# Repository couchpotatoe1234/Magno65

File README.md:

## Magno65
After weeks of hard work, here it is. The first prototype of the Magno65.

It will use N52 Neodymium magnets that are 5mmx2mm in the PCB and on the bottom of the case, allowing the plate and the PCB to levitate. 

The case itself is two parts, so it is 3D-printable. I currently have some untested firmware that will be tested when I make this project. Heres the aproximate BOM currently.
| Name                     | Purpose                                            | Quantity | Total Cost (USD) | Link                                                                                                                                                                                                                                                                                                                                                                                                                                                                                                                                                                                                                                                                                                                                                                                                                                                                                                                                                                                                                                                                                                                                                                                                                                                                                                                                                                                | Distributor       |
|--------------------------|----------------------------------------------------|----------|------------------|-------------------------------------------------------------------------------------------------------------------------------------------------------------------------------------------------------------------------------------------------------------------------------------------------------------------------------------------------------------------------------------------------------------------------------------------------------------------------------------------------------------------------------------------------------------------------------------------------------------------------------------------------------------------------------------------------------------------------------------------------------------------------------------------------------------------------------------------------------------------------------------------------------------------------------------------------------------------------------------------------------------------------------------------------------------------------------------------------------------------------------------------------------------------------------------------------------------------------------------------------------------------------------------------------------------------------------------------------------------------------------------|-------------------|
| PCB                      | THE PCB, THE MAIN PART                             | 1        | 22.60            | https://jlcpcb.com                                                                                                                                                                                                                                                                                                                                                                                                                                                                                                                                                                                                                                                                                                                                                                                                                                                                                                                                                                                                                                                                                                                                                                                                                                                                                                                                                                  | JLCPCB            |
| N52 Neodymium magnets    | to levitate the PCB (smallest pack I could find)   | 1        | 12.04            | https://www.greenstuffworld.com/en/neodymium-magnets-n52/503-neodymium-magnets-5x2mm-50-units-n52.html                                                                                                                                                                                                                                                                                                                                                                                                                                                                                                                                                                                                                                                                                                                                                                                                                                                                                                                                                                                                                                                                                                                                                                                                                                                                              | Green Stuff World |
| Keyboard Stabilizers     | to stabilize the keycaps                           | 1        | 7.55             | https://www.temu.com/gold-plated-plate-mounted-stabilizer-for-custom-mechanical-keyboard-2u-6-25u-g-601100064817086.html?_oak_mp_inf=EL7%2F2Z6o1ogBGiBhMzZlYTk0MDE5MDM0NmMyODM0NzBlNDU1ZjBkMDlmNCC4grKg2DM%3D&top_gallery_url=https%3A%2F%2Fimg.kwcdn.com%2Fproduct%2Fopen%2Fd60568b099454d8eb8d5ba905d9cdf42-goods.jpeg&spec_gallery_id=393266&refer_page_sn=10009&freesia_scene=2&_oak_freesia_scene=2&_oak_rec_ext_1=NzU1&_oak_gallery_order=289069023%2C1381943868%2C460904097%2C430772795%2C1266147886&search_key=keyboard%20stabilizers&refer_page_el_sn=200049&ab_scene=0&enable_vqr=0&_x_sessn_id=wn14p9w9rk&refer_page_name=search_result&refer_page_id=10009_1776036808997_7foyaswubl                                                                                                                                                                                                                                                                                                                                                                                                                                                                                                                                                                                                                                                                                     | Temu              |
| usb micro to usb-c cable | to connect the keyboard to the computer            | 1        | 2.71             | https://www.temu.com/5a-type-c-to-micro-usb-fast-charging-cable-data-tansmission-stable-current-micro-usb-to-type-c-fast-charging-data-cable-for-samsung-xiaomi-huawei-oppo-vivo-high---data-transfer-stable--flexible-charging-cord-g-601104579509990.html?_oak_name_id=9149517372169643071&_oak_mp_inf=EOb9vIe51ogBGiAyZTAxZWY4OTRiNDI0Njk2ODY5YTBmMDNjYmFjMTRiZCDHubrF2TM%3D&top_gallery_url=https%3A%2F%2Fimg.kwcdn.com%2Fproduct%2Ffancy%2Fda51984b-53ff-40e5-8730-5d485981ee59.jpg&spec_gallery_id=261625&refer_page_sn=10009&freesia_scene=2&_oak_freesia_scene=2&_oak_rec_ext_1=Mjcx&_oak_gallery_order=2142591388%2C62159532%2C433164792%2C413324470%2C631688684&search_key=USB-micro%20%20to%20USB%20C%20data%20cable&refer_page_el_sn=200049&ab_scene=0&enable_vqr=1&_x_sessn_id=jb5si0zpbp&refer_page_name=search_result&refer_page_id=10009_1776383073866_u557bmamcj                                                                                                                                                                                                                                                                                                                                                                                                                                                                                                   | Temu              |
| Keycaps                  | to cap the keys                                    | 1        | 6.93             | https://www.temu.com/chic-keycaps-with-contour-lines-featuring--cherry-profile-consisting-of-97-keys--double-shot--for---keycaps-have-see-through--and-lines-g-601100242084406.html?top_gallery_url=https%3A%2F%2Fimg.kwcdn.com%2Fproduct%2Ffancy%2Fb366fc6c-a63f-47c5-8457-d1d9722e4f54.jpg&spec_gallery_id=543959&sku_id=17595324095682&share_token=9SXbwjGQVvLN6AO53nGwdSsUjAHTKImzPHW_I8MpLbxXkFdfj7VuzHuMNDMW4RcFgEqpbDA2upZXWQSFJtAKj5j0HpVFpJCpJvDXVilPGBAXoFHNXLZ6pTCILVGUqEs-&_x_vst_scene=adg&_x_ads_sub_channel=shopping&_x_ns_prz_type=-1&_x_ns_sku_id=17595324095682&_x_ns_gid=601100242084406&_x_ads_channel=google&_x_gmc_account=647900107&_x_login_type=Google&_x_ns_gg_lnk_type=adr&_x_ads_account=1919904652&_x_ads_set=23247691873&_x_ads_id=187675937039&_x_ads_creative_id=783286179500&_x_ns_source=g&_x_ns_gclid=CjwKCAjw4ufOBhBkEiwAfuC7-UZCRVvgkzCTDwP36QHYZFekTYgLvvixg20i3j8YRcbgYLOlBl8YVxoCQrMQAvD_BwE&_x_ns_placement=&_x_ns_match_type=&_x_ns_ad_position=&_x_ns_product_id=17595324095682&_x_ns_target=&_x_ns_devicemodel=&_x_ns_wbraid=CkAKCAjwv-LOBhAqEjAADfTDQ57mPWh-82gaj2x_fIcqDOgOiXeyfZ63v2ajT7DN7h4Hyk_YQIfNX7wuApAaAqFg&_x_ns_gbraid=0AAAAAo4mICFO7USGgQmlUADytEljoZTBi&_x_ns_targetid=pla-2449976477415&refer_page_name=kuiper&refer_page_id=13554_1775933032362_l0cclbjv3z&refer_page_sn=13554&_x_sessn_id=g915edwnry&no_cache_id=v32fd | Temu              |
| Pi Pico                  | the brains of the operation                        | 1        | 3.11             | https://www.temu.com/1pc-sensor-module-pico-development-board--pico---supports--python-low-power-consumption--compatible-with--ide-and-csdk-industrial-electronics-no-battery-no-laser-no-power-supply-material-g-601101152060856.html?_oak_name_id=6196207251010431518&_oak_mp_inf=ELiLkqWs1ogBGiBlMDU1NTAzMzAyNTI0YjMwYTU4M2EwYzljOTMxY2Q2MiDKs7bF2TM%3D&top_gallery_url=https%3A%2F%2Fimg.kwcdn.com%2Fproduct%2Ffancy%2F4f114b41-fe38-4c86-ba03-02ec2a3dbbf5.jpg&spec_gallery_id=487416&refer_page_sn=10009&freesia_scene=2&_oak_freesia_scene=2&_oak_rec_ext_1=MjUy&_oak_gallery_order=299434050%2C1788024366%2C1629561563%2C784285033&search_key=raspberry%20pi%20pico%20rp2040&refer_page_el_sn=200049&ab_scene=0&enable_vqr=1&_x_sessn_id=sfkm1vnct9&refer_page_name=search_result&refer_page_id=10009_1776383007634_b0dhtdh5bt                                                                                                                                                                                                                                                                                                                                                                                                                                                                                                                                              | Temu              |
| Male pin headers         | these are to connect the pi to the board           | 1        | 2.27             | https://www.temu.com/dual-row-2-54mm-pitch-male-pin--40-pin-pcb-connector-strip-for--embedded-systems-g-606045468466813.html?_oak_name_id=5308195194819228546&_oak_mp_inf=EP289qaf5okBGiBmYTI0ZDYwMDQ5NTY0NDc5ODE3OTY4Y2JlYzg3MzViNSDv9fOX2DM%3D&top_gallery_url=https%3A%2F%2Fimg.kwcdn.com%2Fproduct%2Fopen%2F71f1f25fde7d4121ad8cf00ed77ffae3-goods.jpeg&spec_gallery_id=513684&refer_page_sn=10009&freesia_scene=2&_oak_freesia_scene=2&_oak_rec_ext_1=MTQ0&_oak_gallery_order=1559177372%2C921529512%2C483001345%2C1617419758%2C2126600602&search_key=20%20pin%20male%20header&refer_page_el_sn=200049&ab_scene=0&enable_vqr=0&refer_page_name=search_result&refer_page_id=10009_1776019078036_leadu12nfu&_x_sessn_id=sfkm1vnct9                                                                                                                                                                                                                                                                                                                                                                                                                                                                                                                                                                                                                                               | Temu              |
| 1N4148                   | the diodes to make the keyboard work               | 1        | 2.32             | https://www.temu.com/100pcs-1n4148-in4148-do-35-switch-diode-uncharged-other-material-for--g-601100062954719.html?_oak_name_id=417209526502550354&_oak_mp_inf=EN%2Bp6J2o1ogBGiAxNzEzZTYyYzRjYzI0ZmQ1YjZiMWVlNDAyNWZhZDQyNCD44vaX2DM%3D&top_gallery_url=https%3A%2F%2Fimg.kwcdn.com%2Fproduct%2Ffancy%2Fmarket%2Ff59eac153d7334a99a68b11075357811_5hFREXPAsaAaP.jpg&spec_gallery_id=1&refer_page_sn=10009&freesia_scene=2&_oak_freesia_scene=2&_oak_rec_ext_1=MTU0&_oak_gallery_order=1414014030%2C1973228982%2C2050237809%2C1124613986%2C850893309&search_key=1N914&refer_page_el_sn=200049&ab_scene=0&enable_vqr=0&refer_page_name=search_result&refer_page_id=10009_1776019078036_leadu12nfu&_x_sessn_id=sfkm1vnct9                                                                                                                                                                                                                                                                                                                                                                                                                                                                                                                                                                                                                                                               | Temu              |
| Key switches             | these are the whole point of a mechanical keyboard | 1        | 19.99            | https://www.wobkey.com/collections/all/products/keebmonkey-wobkey-rainy75-pre-lubed-hmx-jwk-switches                                                                                                                                                                                                                                                                                                                                                                                                                                                                                                                                                                                                                                                                                                                                                                                                                                                                                                                                                                                                                                                                                                                                                                                                                                                                                | WOBKEY            |

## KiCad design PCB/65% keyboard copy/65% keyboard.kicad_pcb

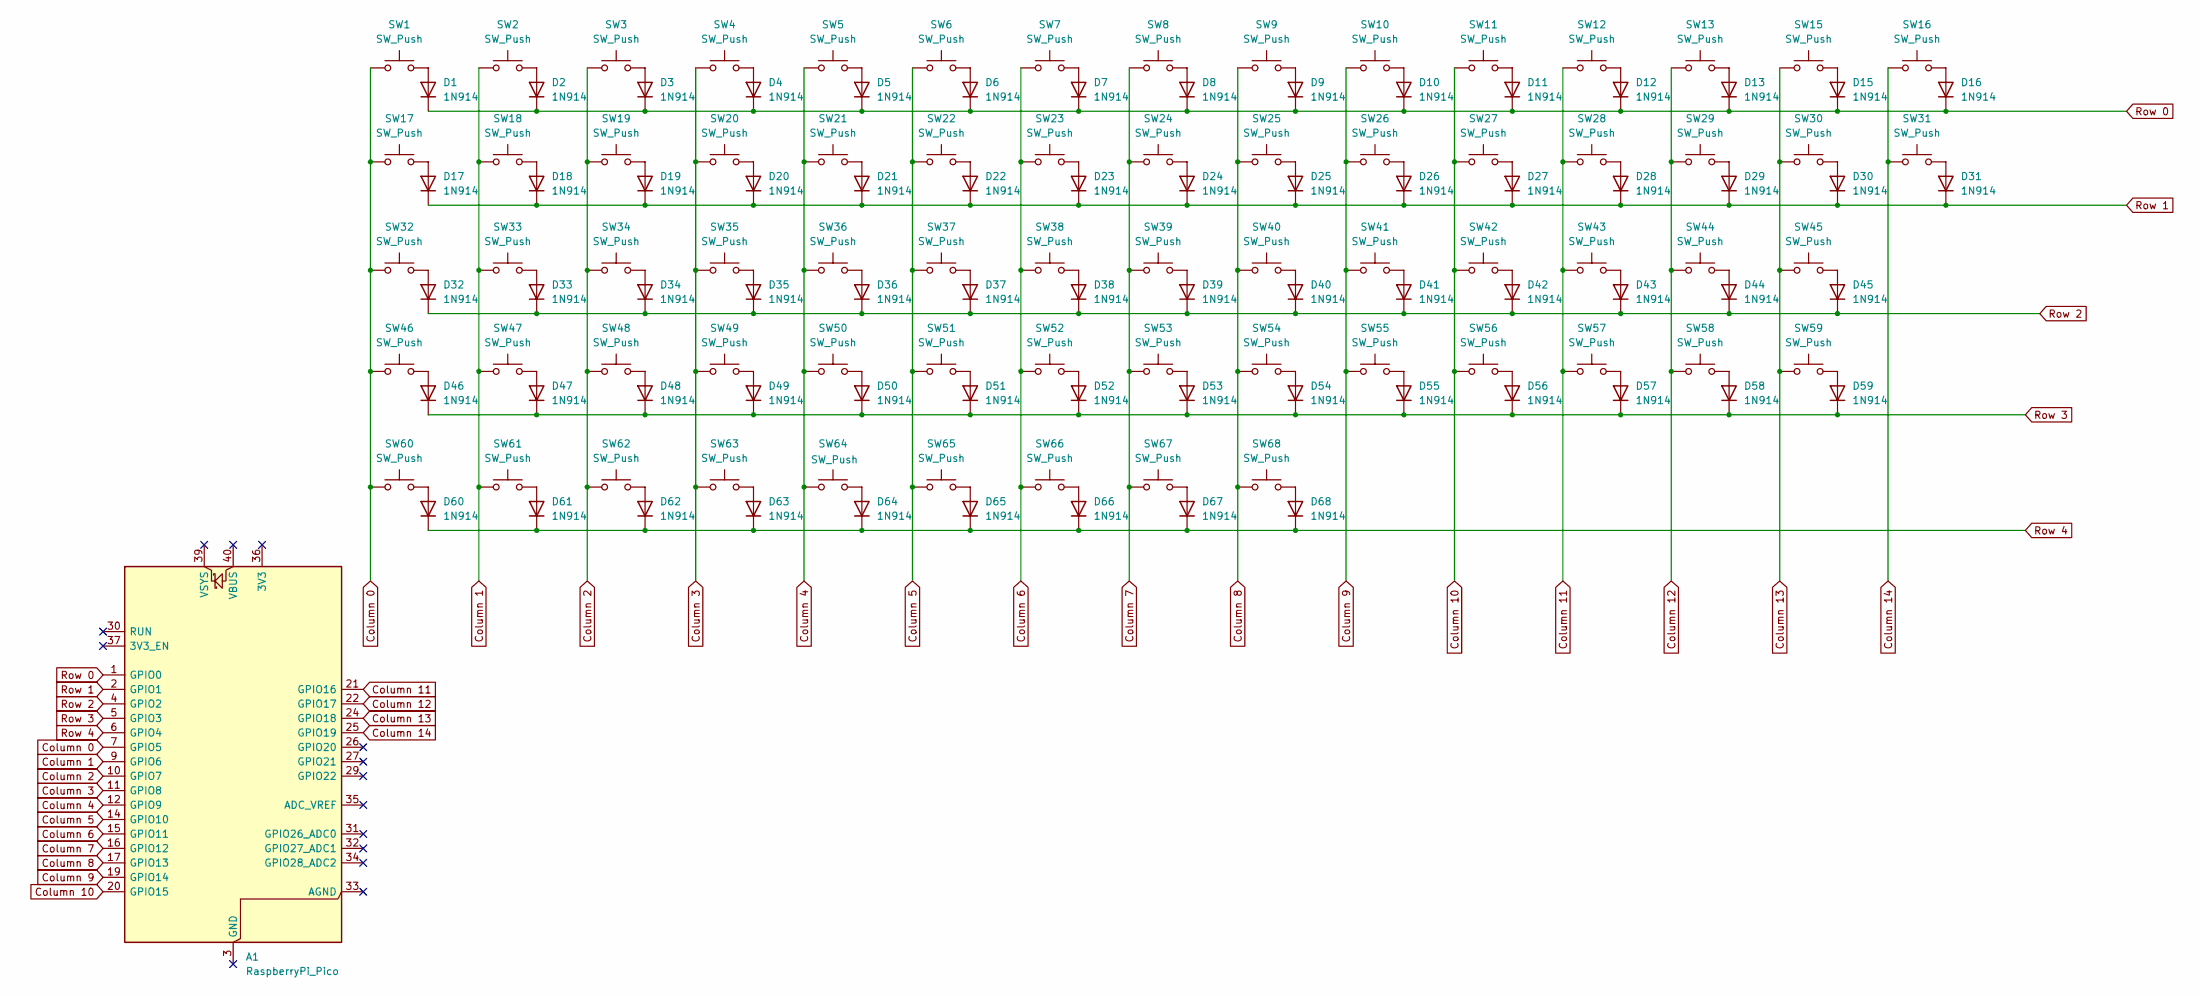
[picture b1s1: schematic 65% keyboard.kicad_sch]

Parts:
A1: RaspberryPi_Pico; RaspberryPi_Pico_Common_Unspecified
D1, D2, D3, D4, D5, D6, D7, D8, D9, D10, D11, D12, D13, D15, D16, D17, D18, D19, D20, D21, D22, D23, D24, D25, D26, D27, D28, D29, D30, D31, D32, D33, D34, D35, D36, D37, D38, D39, D40, D41, D42, D43, D44, D45, D46, D47, D48, D49, D50, D51, D52, D53, D54, D55, D56, D57, D58, D59, D60, D61, D62, D63, D64, D65, D66, D67, D68: 1N914; D_DO-35_SOD27_P7.62mm_Horizontal
SW1, SW2, SW3, SW4, SW5, SW6, SW7, SW8, SW9, SW10, SW11, SW12, SW13, SW16, SW17, SW18, SW19, SW20, SW21, SW22, SW23, SW24, SW25, SW26, SW27, SW28, SW29, SW30, SW31, SW32, SW33, SW34, SW35, SW36, SW37, SW38, SW39, SW40, SW41, SW42, SW43, SW45, SW47, SW48, SW49, SW50, SW51, SW52, SW53, SW54, SW55, SW56, SW57, SW58, SW59, SW60, SW61, SW64, SW65, SW66, SW67, SW68: SW_Push; SW_Cherry_MX_1.00u_PCB
SW15: SW_Push; SW_Cherry_MX_2.00u_Plate
SW44, SW46: SW_Push; SW_Cherry_MX_2.25u_Plate
SW62: SW_Push; SW_Cherry_MX_1.00u_Plate
SW63: SW_Push; SW_Cherry_MX_6.25u_Plate

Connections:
Column 0: A1.7 (GPIO5), SW1.1, SW17.1, SW32.1, SW46.1, SW60.1
Column 1: A1.9 (GPIO6), SW2.1, SW18.1, SW33.1, SW47.1, SW61.1
Column 2: A1.10 (GPIO7), SW3.1, SW19.1, SW34.1, SW48.1, SW62.1
Column 3: A1.11 (GPIO8), SW4.1, SW20.1, SW35.1, SW49.1, SW63.1
Column 4: A1.12 (GPIO9), SW5.1, SW21.1, SW36.1, SW50.1, SW64.1
Column 5: A1.14 (GPIO10), SW6.1, SW22.1, SW37.1, SW51.1, SW65.1
Column 6: A1.15 (GPIO11), SW7.1, SW23.1, SW38.1, SW52.1, SW66.1
Column 7: A1.16 (GPIO12), SW8.1, SW24.1, SW39.1, SW53.1, SW67.1
Column 8: A1.17 (GPIO13), SW9.1, SW25.1, SW40.1, SW54.1, SW68.1
Column 9: A1.19 (GPIO14), SW10.1, SW26.1, SW41.1, SW55.1
Column 10: A1.20 (GPIO15), SW11.1, SW27.1, SW42.1, SW56.1
Column 11: A1.21 (GPIO16), SW12.1, SW28.1, SW43.1, SW57.1
Column 12: A1.22 (GPIO17), SW13.1, SW29.1, SW44.1, SW58.1
Column 13: A1.24 (GPIO18), SW15.1, SW30.1, SW45.1, SW59.1
Column 14: A1.25 (GPIO19), SW16.1, SW31.1
unnamed: D1.2 (A), SW1.2
unnamed: D2.2 (A), SW2.2
unnamed: D3.2 (A), SW3.2
unnamed: D4.2 (A), SW4.2
unnamed: D5.2 (A), SW5.2
unnamed: D6.2 (A), SW6.2
unnamed: D7.2 (A), SW7.2
unnamed: D8.2 (A), SW8.2
unnamed: D9.2 (A), SW9.2
unnamed: D10.2 (A), SW10.2
unnamed: D11.2 (A), SW11.2
unnamed: D12.2 (A), SW12.2
unnamed: D13.2 (A), SW13.2
unnamed: D15.2 (A), SW15.2
unnamed: D16.2 (A), SW16.2
unnamed: D17.2 (A), SW17.2
unnamed: D18.2 (A), SW18.2
unnamed: D19.2 (A), SW19.2
unnamed: D20.2 (A), SW20.2
unnamed: D21.2 (A), SW21.2
unnamed: D22.2 (A), SW22.2
unnamed: D23.2 (A), SW23.2
unnamed: D24.2 (A), SW24.2
unnamed: D25.2 (A), SW25.2
unnamed: D26.2 (A), SW26.2
unnamed: D27.2 (A), SW27.2
unnamed: D28.2 (A), SW28.2
unnamed: D29.2 (A), SW29.2
unnamed: D30.2 (A), SW30.2
unnamed: D31.2 (A), SW31.2
unnamed: D32.2 (A), SW32.2
unnamed: D33.2 (A), SW33.2
unnamed: D34.2 (A), SW34.2
unnamed: D35.2 (A), SW35.2
unnamed: D36.2 (A), SW36.2
unnamed: D37.2 (A), SW37.2
unnamed: D38.2 (A), SW38.2
unnamed: D39.2 (A), SW39.2
unnamed: D40.2 (A), SW40.2
unnamed: D41.2 (A), SW41.2
unnamed: D42.2 (A), SW42.2
unnamed: D43.2 (A), SW43.2
unnamed: D44.2 (A), SW44.2
unnamed: D45.2 (A), SW45.2
unnamed: D46.2 (A), SW46.2
unnamed: D47.2 (A), SW47.2
unnamed: D48.2 (A), SW48.2
unnamed: D49.2 (A), SW49.2
unnamed: D50.2 (A), SW50.2
unnamed: D51.2 (A), SW51.2
unnamed: D52.2 (A), SW52.2
unnamed: D53.2 (A), SW53.2
unnamed: D54.2 (A), SW54.2
unnamed: D55.2 (A), SW55.2
unnamed: D56.2 (A), SW56.2
unnamed: D57.2 (A), SW57.2
unnamed: D58.2 (A), SW58.2
unnamed: D59.2 (A), SW59.2
unnamed: D60.2 (A), SW60.2
unnamed: D61.2 (A), SW61.2
unnamed: D62.2 (A), SW62.2
unnamed: D63.2 (A), SW63.2
unnamed: D64.2 (A), SW64.2
unnamed: D65.2 (A), SW65.2
unnamed: D66.2 (A), SW66.2
unnamed: D67.2 (A), SW67.2
unnamed: D68.2 (A), SW68.2
Row 0: A1.1 (GPIO0), D1.1 (K), D2.1 (K), D3.1 (K), D4.1 (K), D5.1 (K), D6.1 (K), D7.1 (K), D8.1 (K), D9.1 (K), D10.1 (K), D11.1 (K), D12.1 (K), D13.1 (K), D15.1 (K), D16.1 (K)
Row 1: A1.2 (GPIO1), D17.1 (K), D18.1 (K), D19.1 (K), D20.1 (K), D21.1 (K), D22.1 (K), D23.1 (K), D24.1 (K), D25.1 (K), D26.1 (K), D27.1 (K), D28.1 (K), D29.1 (K), D30.1 (K), D31.1 (K)
Row 2: A1.4 (GPIO2), D32.1 (K), D33.1 (K), D34.1 (K), D35.1 (K), D36.1 (K), D37.1 (K), D38.1 (K), D39.1 (K), D40.1 (K), D41.1 (K), D42.1 (K), D43.1 (K), D44.1 (K), D45.1 (K)
Row 3: A1.5 (GPIO3), D46.1 (K), D47.1 (K), D48.1 (K), D49.1 (K), D50.1 (K), D51.1 (K), D52.1 (K), D53.1 (K), D54.1 (K), D55.1 (K), D56.1 (K), D57.1 (K), D58.1 (K), D59.1 (K)
Row 4: A1.6 (GPIO4), D60.1 (K), D61.1 (K), D62.1 (K), D63.1 (K), D64.1 (K), D65.1 (K), D66.1 (K), D67.1 (K), D68.1 (K)

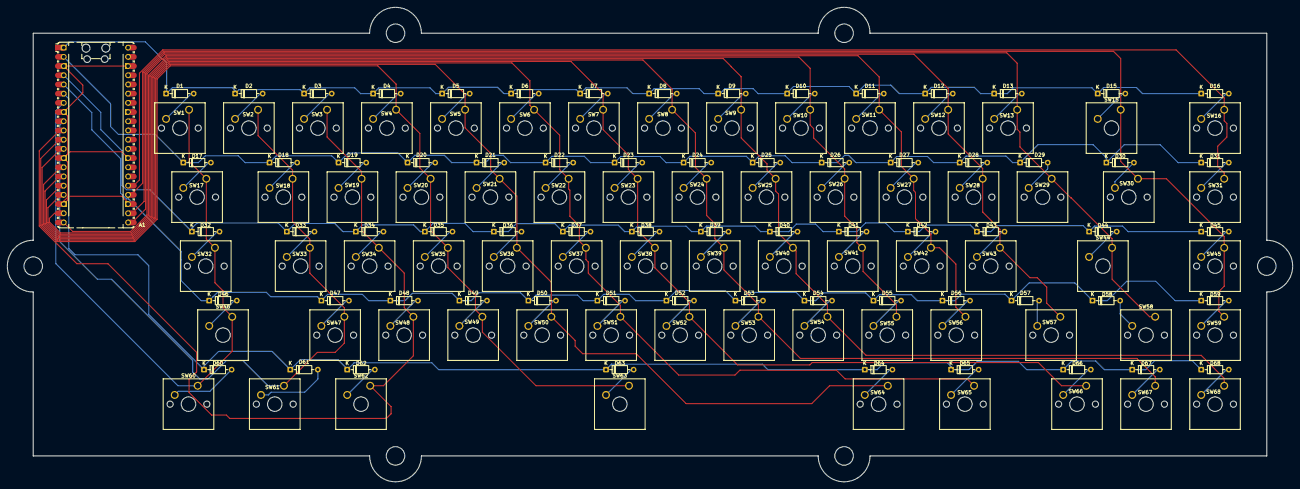
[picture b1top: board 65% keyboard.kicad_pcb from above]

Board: 2 copper layers, 354.8 x 131.0 mm, 135 parts (0 on the bottom side), 87 nets.

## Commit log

2026-04-17 adding BOM
2026-04-17 firmware & case
2026-04-17 README
2026-04-17 Case update
